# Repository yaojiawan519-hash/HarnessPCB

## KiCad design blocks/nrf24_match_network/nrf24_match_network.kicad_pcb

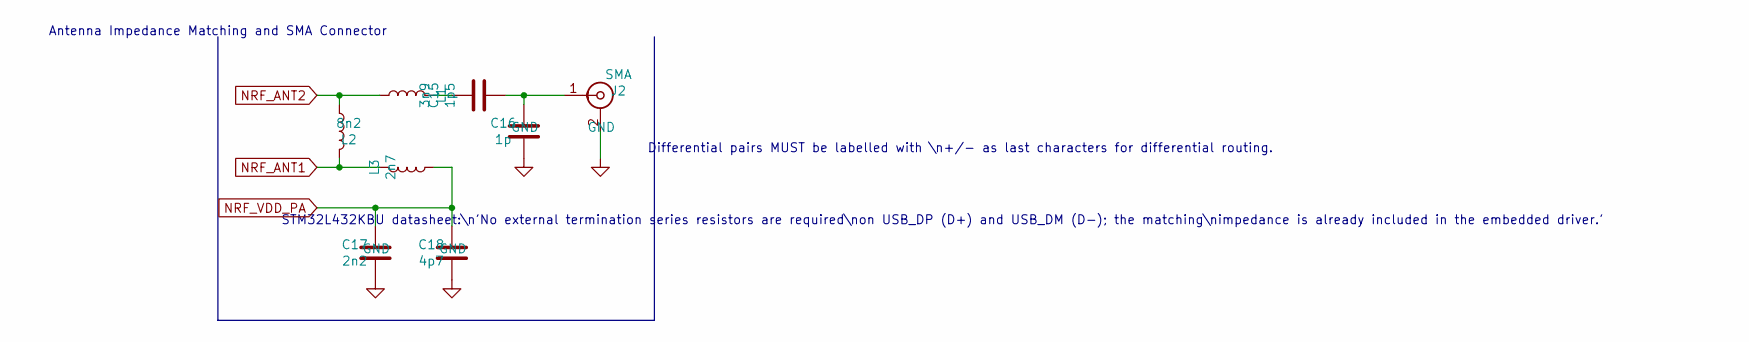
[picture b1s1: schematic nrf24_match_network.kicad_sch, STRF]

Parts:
C15: 1p5; C_0402_1005Metric
C16: 1p; C_0402_1005Metric
C17: 2n2; C_0402_1005Metric
C18: 4p7; C_0402_1005Metric
J2: SMA; SMA_Samtec_SMA-J-P-X-ST-EM1_EdgeMount
L1: 3n9; L_0402_1005Metric
L2: 8n2; L_0402_1005Metric
L3: 2n7; L_0402_1005Metric

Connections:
GND: C16.1, C17.1, C18.1, J2.2 (Ext)
NRF_ANT1: L2.2, L3.2
NRF_ANT2: L1.1, L2.1
NRF_VDD_PA: C17.2, C18.2, L3.1
unnamed: C15.1, C16.2, J2.1 (In)
unnamed: C15.2, L1.2

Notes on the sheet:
Differential pairs MUST be labelled with \n+/- as last characters for differential routing.
STM32L432KBU datasheet:\n'No external termination series resistors are required\non USB_DP (D+) and USB_DM (D-); the matching\nimpedance is already included in the embedded driver.'
Antenna Impedance Matching and SMA Connector

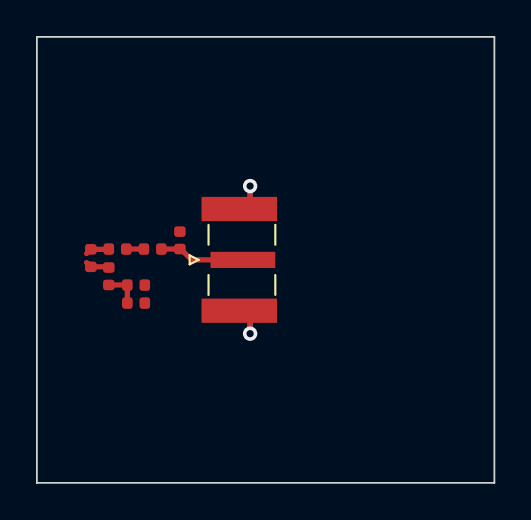
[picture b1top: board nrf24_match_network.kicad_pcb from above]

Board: 2 copper layers, 25.4 x 24.8 mm, 8 parts (0 on the bottom side), 6 nets.

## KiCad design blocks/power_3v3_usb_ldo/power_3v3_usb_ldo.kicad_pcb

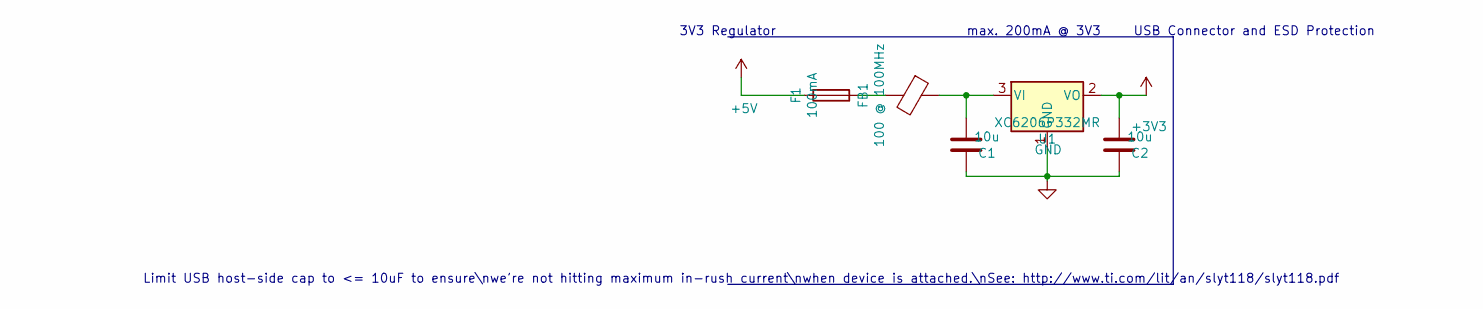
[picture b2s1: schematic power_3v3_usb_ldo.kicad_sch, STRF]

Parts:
C1, C2: 10u; C_0603_1608Metric
F1: 100mA; Fuse_1206_3216Metric
FB1: 100 @ 100MHz; L_0805_2012Metric
U1: XC6206P332MR; SOT-23

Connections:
+3V3: C2.1, U1.2 (VO)
+5V: F1.2
GND: C1.2, C2.2, U1.1 (GND)
unnamed: C1.1, FB1.1, U1.3 (VI)
unnamed: F1.1, FB1.2

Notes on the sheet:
Limit USB host-side cap to <= 10uF to ensure\nwe're not hitting maximum in-rush current\nwhen device is attached.\nSee: http://www.ti.com/lit/an/slyt118/slyt118.pdf
3V3 Regulator
USB Connector and ESD Protection
max. 200mA @ 3V3

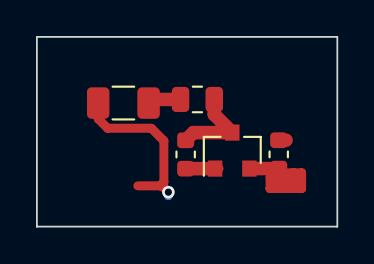
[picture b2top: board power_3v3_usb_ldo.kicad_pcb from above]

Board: 2 copper layers, 16.7 x 10.5 mm, 5 parts (0 on the bottom side), 4 nets.

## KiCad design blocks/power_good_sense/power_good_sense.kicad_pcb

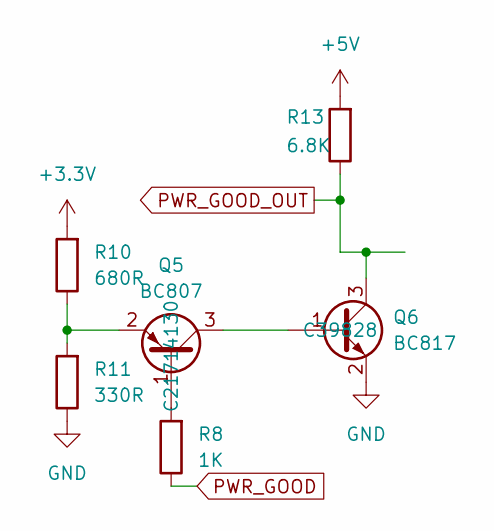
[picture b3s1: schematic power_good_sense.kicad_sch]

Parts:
Q5: BC807; SOT-23
Q6: BC817; SOT-23
R8: 1K; R_0805_2012Metric
R10: 680R; R_0805_2012Metric
R11: 330R; R_0805_2012Metric
R13: 6.8K; R_0805_2012Metric

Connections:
+3.3V: R10.2
BULK_VIN: R13.2
GND: Q6.2 (E), R11.1
unnamed: Q5.1 (B), R8.2
unnamed: Q5.3 (C), Q6.1 (B)
unnamed: Q5.2 (E), R10.1, R11.2
PWR_GOOD: R8.1
PWR_GOOD_OUT: Q6.3 (C), R13.1

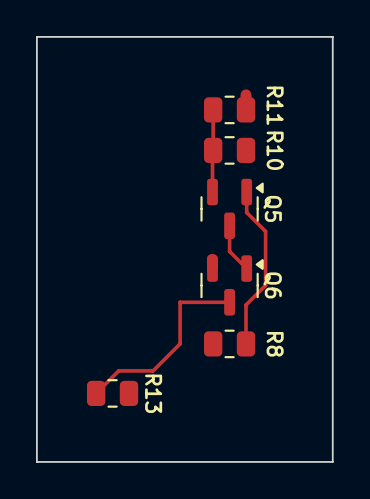
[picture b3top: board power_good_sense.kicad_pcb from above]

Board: 2 copper layers, 16.4 x 23.6 mm, 6 parts (0 on the bottom side), 5 nets.

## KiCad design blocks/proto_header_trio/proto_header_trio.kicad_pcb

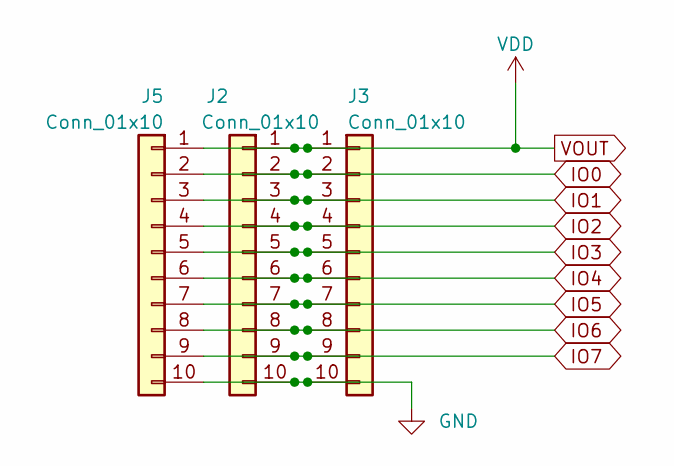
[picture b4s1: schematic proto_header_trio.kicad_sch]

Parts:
J2: Conn_01x10; PinSocket_1x10_P2.54mm_Horizontal
J3: Conn_01x10; PinHeader_1x10_P2.54mm_Vertical_No_Silk
J5: Conn_01x10; PinHeader_1x10_P2.54mm_Vertical_Reduced_2

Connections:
GND: J2.10, J3.10, J5.10
IO0: J2.2, J3.2, J5.2
IO1: J2.3, J3.3, J5.3
IO2: J2.4, J3.4, J5.4
IO3: J2.5, J3.5, J5.5
IO4: J2.6, J3.6, J5.6
IO5: J2.7, J3.7, J5.7
IO6: J2.8, J3.8, J5.8
IO7: J2.9, J3.9, J5.9
VOUT: J2.1, J3.1, J5.1

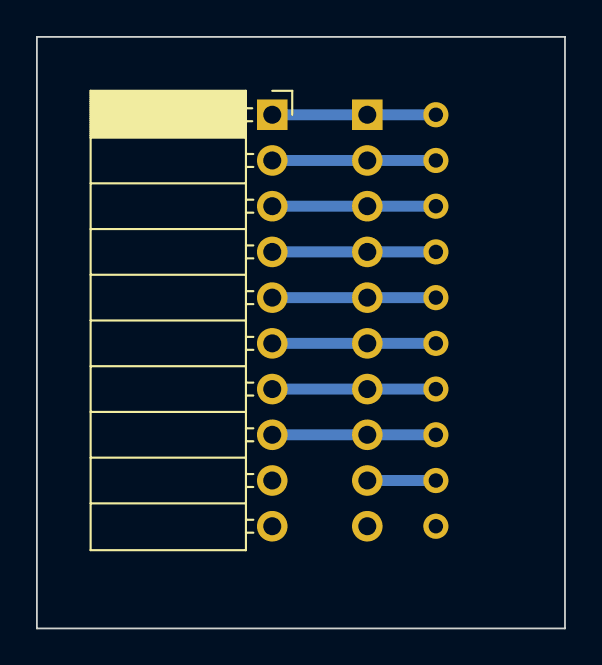
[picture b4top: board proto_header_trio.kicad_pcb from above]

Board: 2 copper layers, 29.3 x 32.9 mm, 3 parts (0 on the bottom side), 10 nets.

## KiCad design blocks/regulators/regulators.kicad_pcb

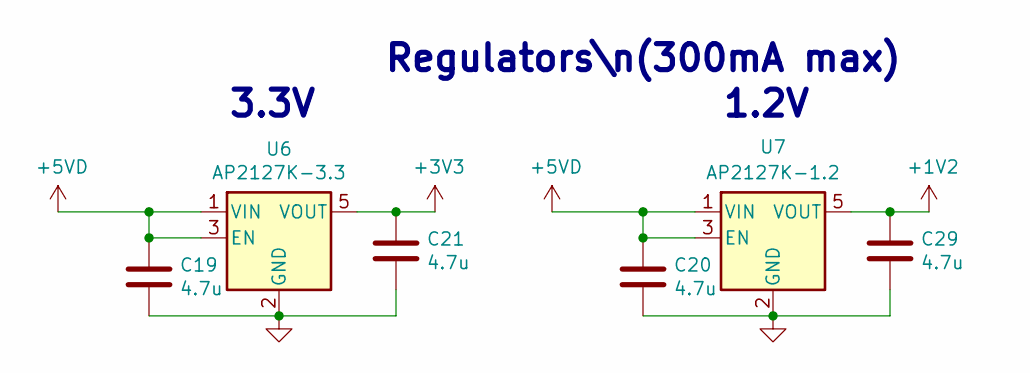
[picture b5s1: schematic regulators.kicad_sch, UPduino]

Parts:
C19, C20, C21, C29: 4.7u; C_0603_1608Metric
U6: AP2127K-3.3; SOT-23-5
U7: AP2127K-1.2; SOT-23-5

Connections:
+1V2: C29.1, U7.5 (VOUT)
+3V3: C21.1, U6.5 (VOUT)
+5VD: C19.1, C20.1, U6.1 (VIN), U6.3 (EN), U7.1 (VIN), U7.3 (EN)
GND: C19.2, C20.2, C21.2, C29.2, U6.2 (GND), U7.2 (GND)

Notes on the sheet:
1.2V
3.3V
Regulators\n(300mA max)

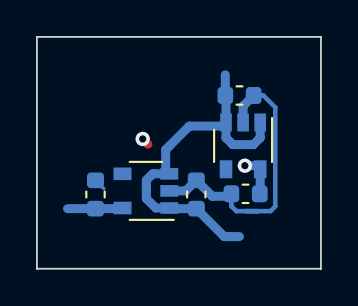
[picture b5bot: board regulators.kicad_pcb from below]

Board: 4 copper layers, 15.8 x 12.9 mm, 6 parts (6 on the bottom side), 4 nets.
